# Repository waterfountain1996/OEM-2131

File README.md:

# OEM-2131

I plan on turning this into a Eurorack module but for now it's a breadboard-compatible prototype
board.

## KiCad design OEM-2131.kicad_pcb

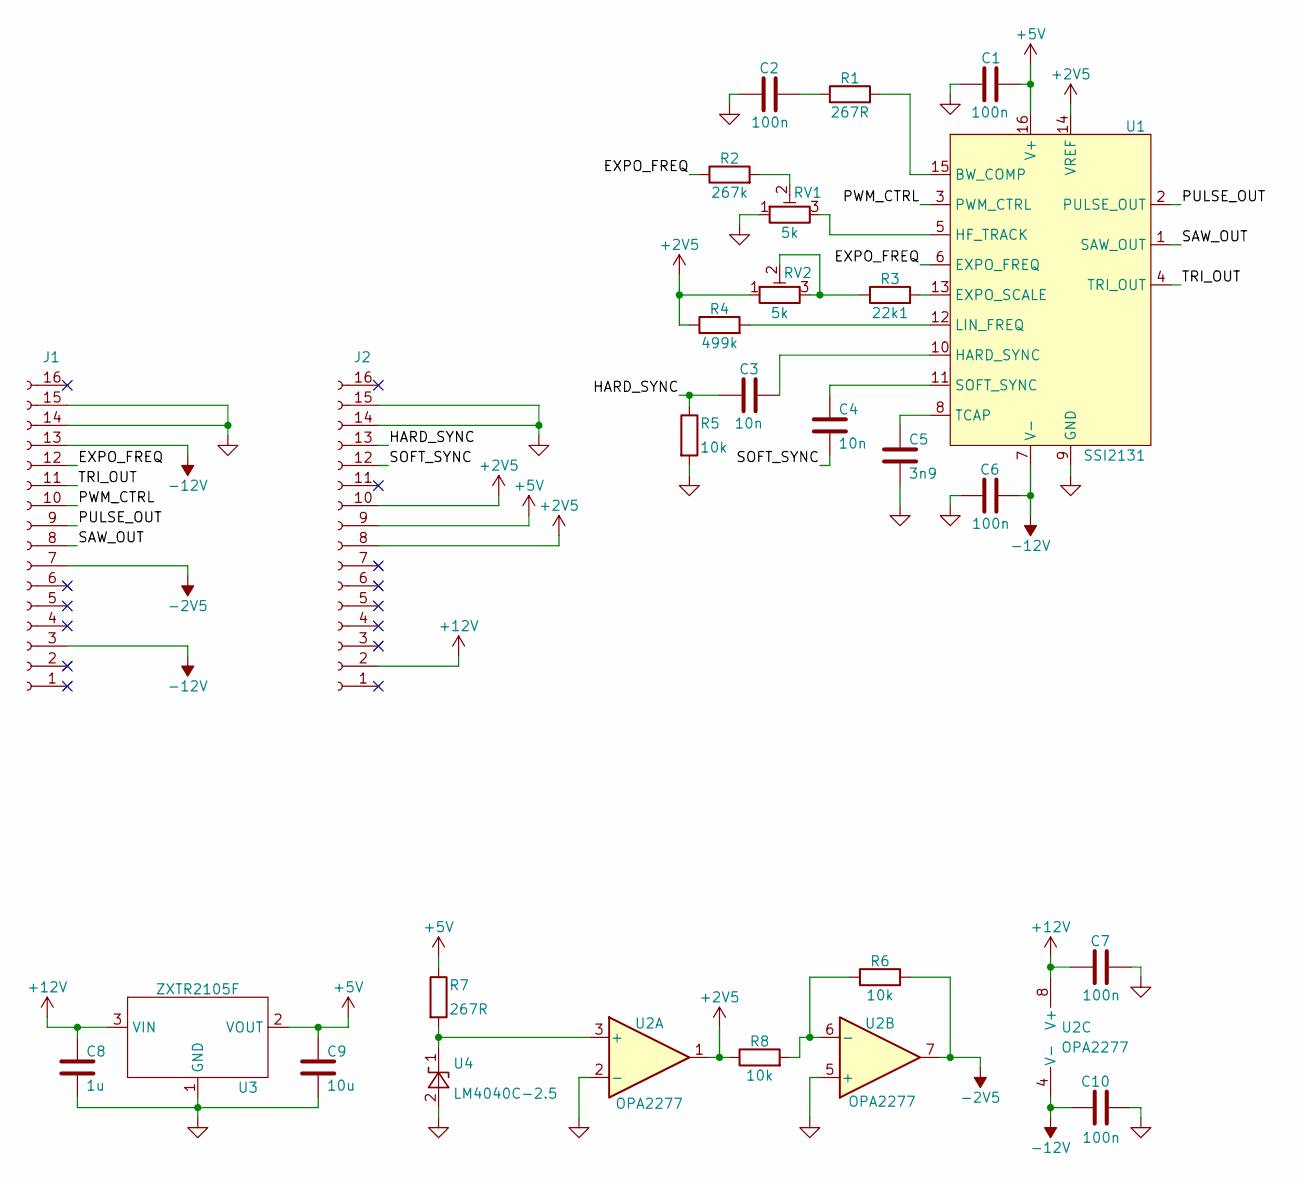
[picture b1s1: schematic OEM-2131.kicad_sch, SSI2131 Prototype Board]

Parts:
C1, C2, C6, C7, C10: 100n; C_0805_2012Metric_Pad1.18x1.45mm_HandSolder
C3, C4: 10n; C_0805_2012Metric_Pad1.18x1.45mm_HandSolder
C5: 3n9; C_0805_2012Metric_Pad1.18x1.45mm_HandSolder
C8: 1u; C_0805_2012Metric_Pad1.18x1.45mm_HandSolder
C9: 10u; C_0805_2012Metric_Pad1.18x1.45mm_HandSolder
J1, J2: Conn_01x16_Socket; PinSocket_1x16_P2.54mm_Vertical
R1, R7: 267R; R_0805_2012Metric_Pad1.20x1.40mm_HandSolder
R2: 267k; R_0805_2012Metric_Pad1.20x1.40mm_HandSolder
R3: 22k1; R_0805_2012Metric_Pad1.20x1.40mm_HandSolder
R4: 499k; R_0805_2012Metric_Pad1.20x1.40mm_HandSolder
R5, R6, R8: 10k; R_0805_2012Metric_Pad1.20x1.40mm_HandSolder
RV1, RV2: 5k; Potentiometer_Bourns_3296W_Vertical
U1: SSI2131; SOIC-16_3.9x9.9mm_P1.27mm
U2: OPA2277; SOIC-8_3.9x4.9mm_P1.27mm
U3: ZXTR2105F; SOT-23
U4: LM4040C-2.5; SOT-23

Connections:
+2V5: J2.8, J2.10, R4.1, R8.1, RV2.1, U1.14 (VREF), U2.1
+5V: C1.1, C9.1, J2.9, R7.1, U1.16 (V+), U3.2 (VOUT)
+12V: C7.1, C8.1, J2.2, U2.8 (V+), U3.3 (VIN)
-2V5: J1.7, R6.2, U2.7
-12V: C6.2, C10.1, J1.3, J1.13, U1.7 (V-), U2.4 (V-)
/EXPO_FREQ: J1.12, R2.1, U1.6 (EXPO_FREQ)
/HARD_SYNC: C3.1, J2.13, R5.1
/PULSE_OUT: J1.9, U1.2 (PULSE_OUT)
/PWM_CTRL: J1.10, U1.3 (PWM_CTRL)
/SAW_OUT: J1.8, U1.1 (SAW_OUT)
/SOFT_SYNC: C4.2, J2.12
/TRI_OUT: J1.11, U1.4 (TRI_OUT)
GND: C1.2, C2.1, C5.2, C6.1, C7.2, C8.2, C9.2, C10.2, J1.14, J1.15, J2.14, J2.15, R5.2, RV1.1, U1.9 (GND), U2.2 (-), U2.5 (+), U3.1 (GND), U4.2 (A)
unnamed: C2.2, R1.1
unnamed: R2.2, RV1.2
unnamed: R3.1, RV2.2, RV2.3
unnamed: R1.2, U1.15 (BW_COMP)
unnamed: R3.2, U1.13 (EXPO_SCALE)
unnamed: C3.2, U1.10 (HARD_SYNC)
unnamed: RV1.3, U1.5 (HF_TRACK)
unnamed: R4.2, U1.12 (LIN_FREQ)
unnamed: C4.1, U1.11 (SOFT_SYNC)
unnamed: C5.1, U1.8 (TCAP)
unnamed: R7.2, U2.3 (+), U4.1 (K)
unnamed: R6.1, R8.2, U2.6 (-)

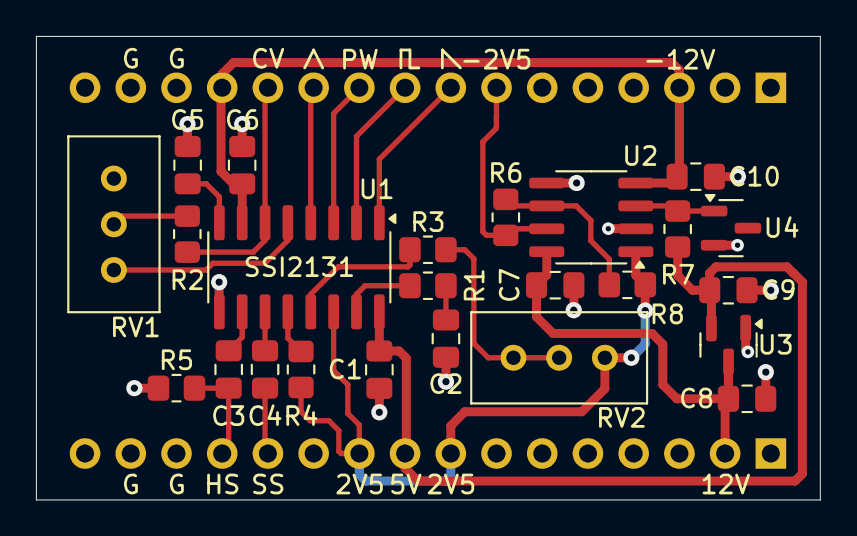
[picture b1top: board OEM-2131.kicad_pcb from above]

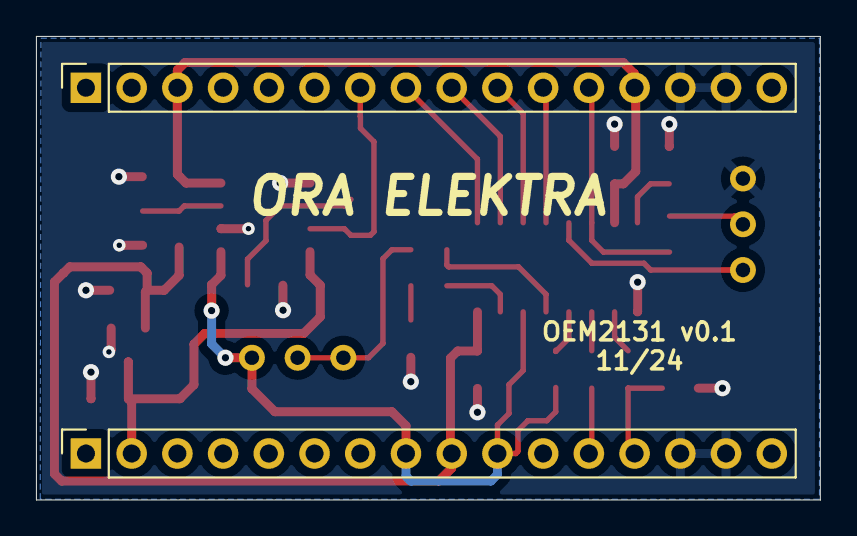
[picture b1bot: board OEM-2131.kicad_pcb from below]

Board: 2 copper layers, 43.5 x 25.8 mm, 26 parts (2 on the bottom side), 25 nets.
